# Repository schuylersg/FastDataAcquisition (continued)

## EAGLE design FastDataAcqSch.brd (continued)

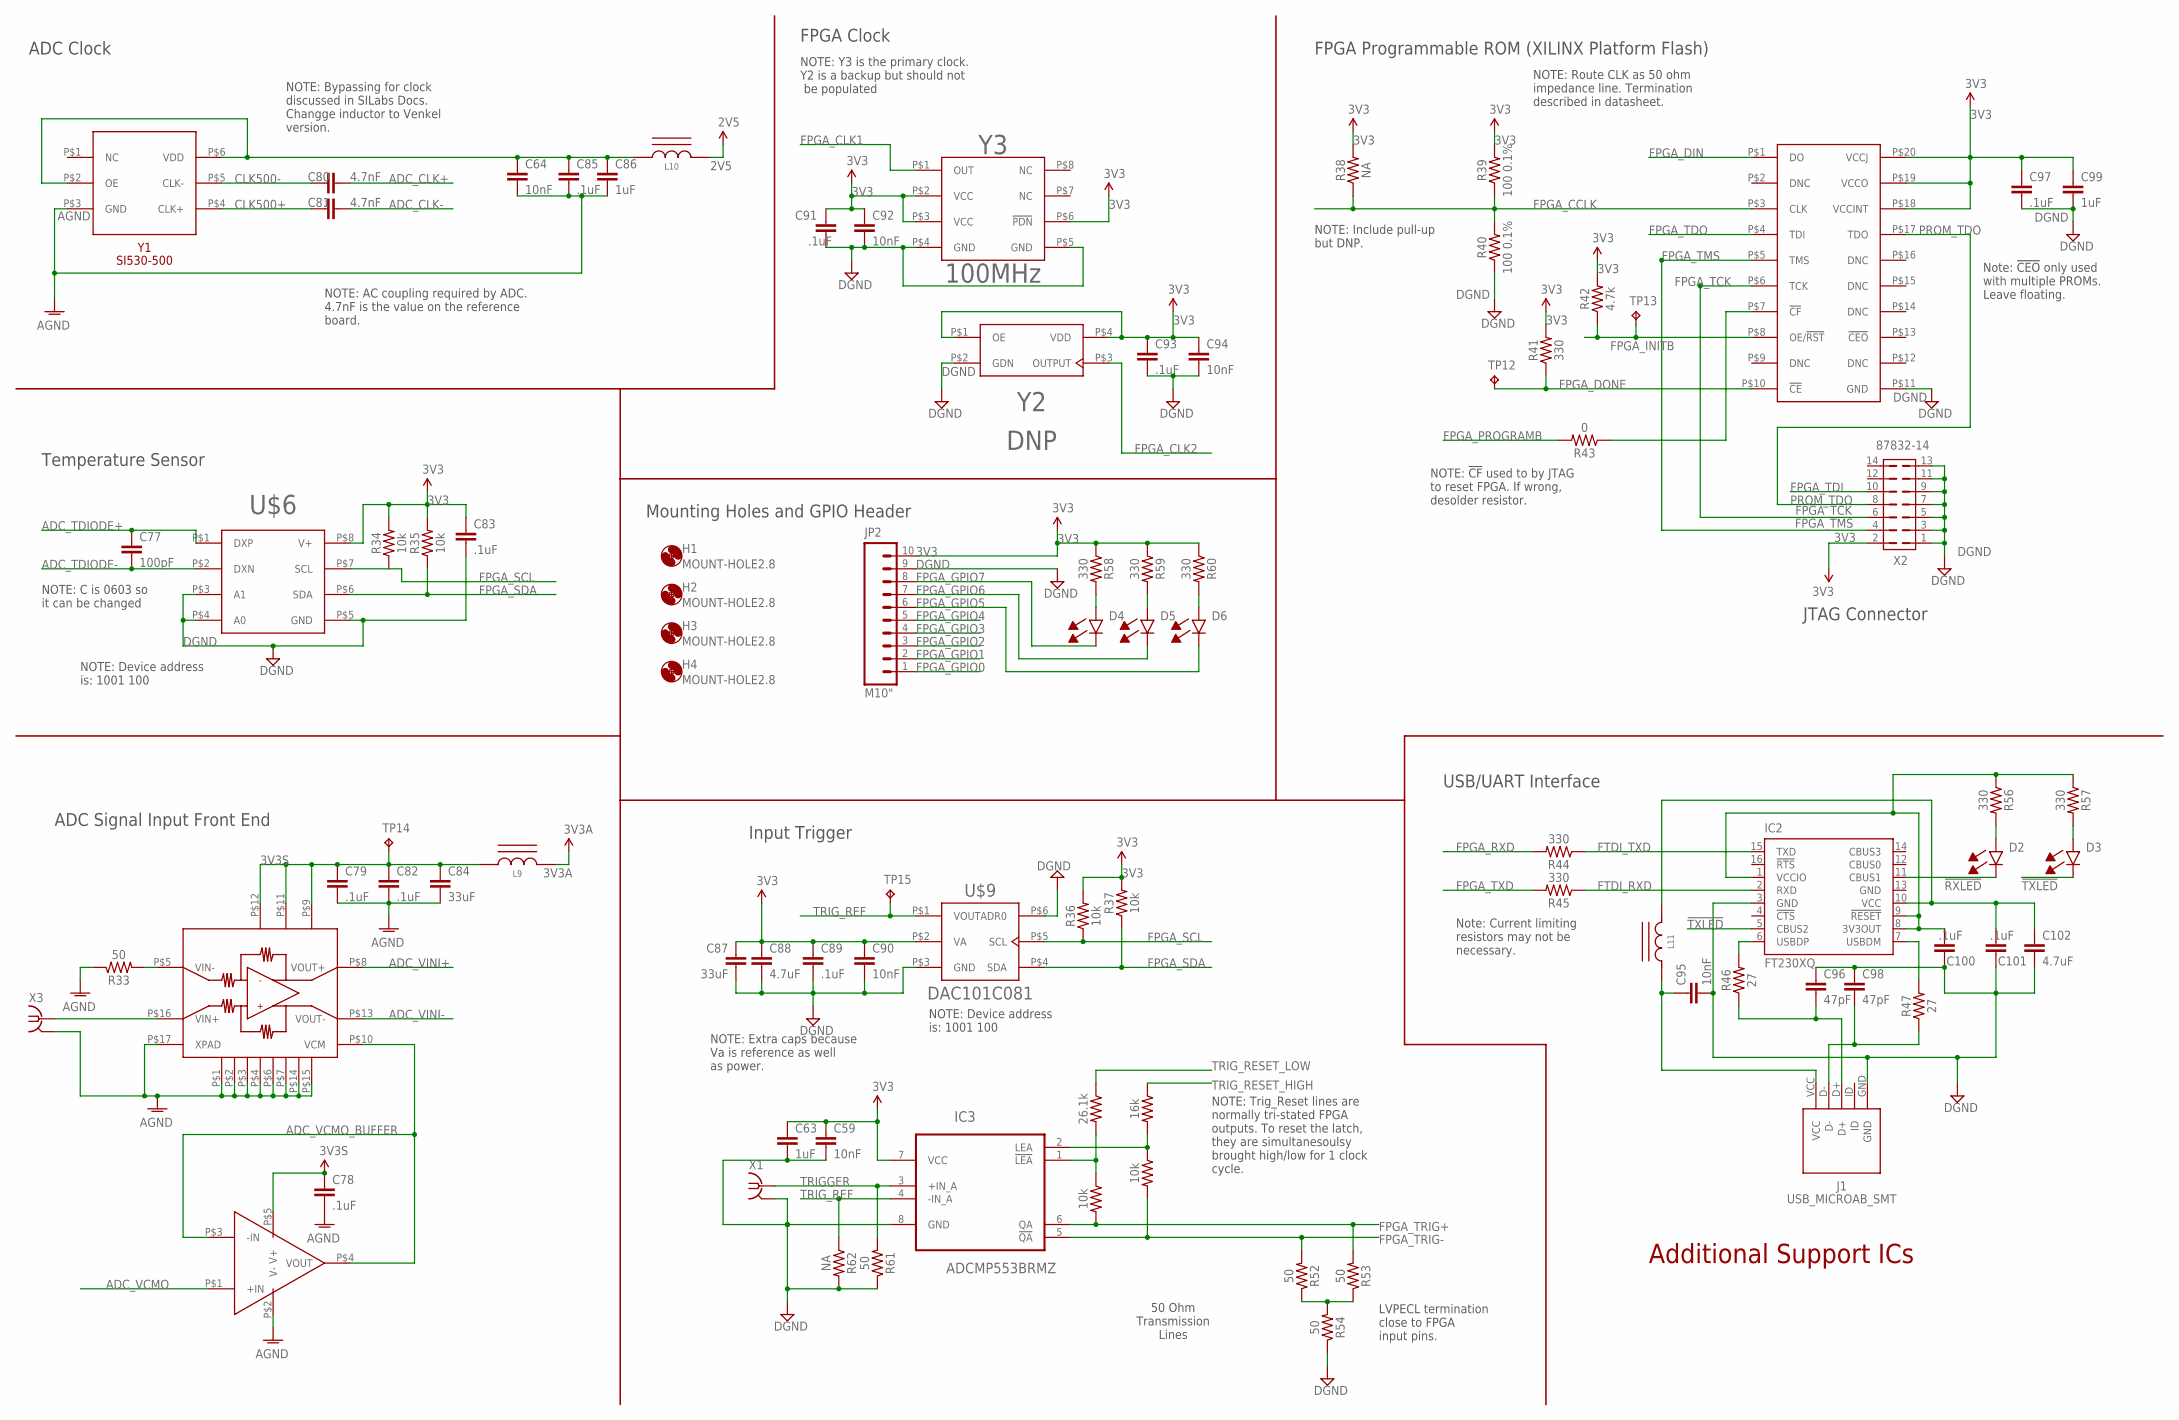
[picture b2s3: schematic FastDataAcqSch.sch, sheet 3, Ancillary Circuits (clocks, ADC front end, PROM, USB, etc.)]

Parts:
C59, C64, C90, C92, C94, C95: 10nF; C0201; PARTNUMBER 445-1793-1-ND
C63, C86, C99: 1uF; 0204REVERSE; PARTNUMBER 445-9091-1-ND
C77: 100pF; C0603; PARTNUMBER 1276-1295-1-ND
C78, C79, C82, C83, C85, C89, C91, C93, C97, C100, C101: .1uF; 0204REVERSE; PARTNUMBER 587-2152-1-ND
C80, C81: 4.7nF; C0201; PARTNUMBER 445-1795-1-ND
C84, C87: 33uF; 0805; PARTNUMBER 445-8238-1-ND
C88, C102: 4.7uF; 0306REVERSE; PARTNUMBER 445-13745-1-ND
C96, C98: 47pF; C0201; PARTNUMBER 445-1782-1-ND
D2, D5: LED_0603_GREEN; 0603_LED
D3, D4: LED_0603_BLUE; 0603_LED
D6: LED_0603_RED; 0603_LED
H1, H2, H3, H4: MOUNT-HOLE2.8; 2,8
IC2: FT230XQ; QFN16
IC3: ADCMP553BRMZ; SOP65P490X110-8N
J1: USB_MICROAB_SMT; USB_MICROAB_SMT_1
JP2: M10"; 1X10
L9, L10: FERRITE_BEADS_BLM18SG260; MURATA_BLM18
L11: FERRITE_BEADS_BLM18SG331; MURATA_BLM18
R33, R52, R53, R54, R61: 50; R0201; MANPARTNUMBER RC0603F49R9C
R34, R35, R36, R37: 10k; R0201; MANPARTNUMBER RC0603J103CS
R38: NA; R0603
R39, R40: 100 0.1%; R0402; MANPARTNUMBER ERA-2AEB101X
R41, R44, R45, R56, R57, R58, R59, R60: 330; R0201; MANPARTNUMBER RC0603J331CS
R42: 4.7k; R0201; MANPARTNUMBER ERJ-1GNJ472C
R43: 0; R0603; PARTNUMBER 311-0.0GRCT-ND
R46, R47: 27; R0201; PARTNUMBER 1276-3577-1-ND
R48, R50: 10k; R0603; PARTNUMBER 311-0.0GRCT-ND
R49: 26.1k; R0603; PARTNUMBER 311-0.0GRCT-ND
R51: 16k; R0603; PARTNUMBER 311-0.0GRCT-ND
R62: NA; R0603; PARTNUMBER 311-0.0GRCT-ND
TP12, TP13, TP14, TP15: TPPAD1-13; P1-13
U$6: TMP421; SOT23-8
U$7: LMH6555; 16WQFN
U$8: LMV321SC-70; SC-70
U$9: DAC101C081; SOT23-6
U$10: XCFXXS04; TSSOP20_XILINX
X1, X3: SMA-142-0701-801/806; J502-ND-142-0701-801/806; MANPARTNUMBER 142-0701-801
X2: 87832-14; PARTNUMBER 57J0374
Y1: SI530-500; SI530
Y2: DNP; SI500S
Y3: 100MHz; UMAX8

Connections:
2V5: L10.P$2; also elsewhere on the board
2V5A: C64.1, C85.P$1 (1), C86.P$1 (1), L10.P$1, Y1.P$2 (OE), Y1.P$6 (VDD)
3V3: C59.1, C63.P$1 (1), C83.P$1 (1), C87.1, C88.P$1 (1), C89.P$1 (1), C90.1, C91.P$1 (1), C92.1, C93.P$1 (1), C94.1, C97.P$1 (1), C99.P$1 (1), IC3.7 (VCC), JP2.10, R35.2, R36.2, R37.2, R38.2, R39.2, R41.2, R58.1, R59.1, R60.1, U$6.P$8 (V+), U$9.P$2 (VA), U$10.P$18 (VCCINT), U$10.P$19 (VCCO), U$10.P$20 (VCCJ), X2.2, Y2.P$1 (OE), Y2.P$4 (VDD), Y3.P$2 (VCC), Y3.P$3 (VCC), Y3.P$6 (!PDN); also elsewhere on the board
3V3A: L9.P$2; also elsewhere on the board
3V3S: C78.P$1 (1), C79.P$1 (1), C82.P$1 (1), C84.1, L9.P$1, TP14.TP, U$7.P$9 (VCC), U$7.P$11 (VCC), U$7.P$12 (VCC), U$8.P$5 (V+)
5VUSB: C101.P$2 (2), C102.P$1 (1), IC2.10 (VCC), L11.P$2
5VUSB_CON: C95.1, J1.VCC, L11.P$1
!RXLED: D2.CATHODE, IC2.11 (CBUS1)
!TXLED: D3.CATHODE, IC2.5 (CBUS2)
ADC_CLK+: C80.2; also elsewhere on the board
ADC_CLK-: C81.2; also elsewhere on the board
ADC_TDIODE+: C77.1, U$6.P$1 (DXP); also elsewhere on the board
ADC_TDIODE-: C77.2, U$6.P$2 (DXN); also elsewhere on the board
ADC_VCMO: U$8.P$1 (+IN); also elsewhere on the board
ADC_VCMO_BUFFER: U$7.P$10 (VCM), U$8.P$3 (-IN), U$8.P$4 (VOUT); also elsewhere on the board
ADC_VINI+: U$7.P$8 (VOUT+); also elsewhere on the board
ADC_VINI-: U$7.P$13 (VOUT-); also elsewhere on the board
AGND: C64.2, C78.P$2 (2), C79.P$2 (2), C82.P$2 (2), C84.2, C85.P$2 (2), C86.P$2 (2), R33.1, U$7.P$1 (GND), U$7.P$2 (GND), U$7.P$3 (GND), U$7.P$4 (GND), U$7.P$6 (GND), U$7.P$7 (GND), U$7.P$14 (GND), U$7.P$15 (GND), U$7.P$17 (XPAD), U$8.P$2 (V-), X3.G@1 (2), X3.G@2 (2), X3.G@3 (2), X3.G@4 (2), Y1.P$3 (GND); also elsewhere on the board
CLK500+: C81.1, Y1.P$4 (CLK+)
CLK500-: C80.1, Y1.P$5 (CLK-)
DGND: C59.2, C63.P$2 (2), C83.P$2 (2), C87.2, C88.P$2 (2), C89.P$2 (2), C90.2, C91.P$2 (2), C92.2, C93.P$2 (2), C94.2, C95.2, C96.1, C97.P$2 (2), C98.1, C99.P$2 (2), C100.P$1 (1), C101.P$1 (1), C102.P$2 (2), IC2.3 (GND), IC3.8 (GND), J1.GND, JP2.9, R40.1, R54.1, R61.1, R62.2, U$6.P$3 (A1), U$6.P$4 (A0), U$6.P$5 (GND), U$9.P$3 (GND), U$9.P$6 (ADR0), U$10.P$11 (GND), X1.G@1 (2), X1.G@2 (2), X1.G@3 (2), X1.G@4 (2), X2.1, X2.3, X2.5, X2.7, X2.9, X2.11, X2.13, Y2.P$2 (GDN), Y3.P$4 (GND), Y3.P$5 (GND); also elsewhere on the board
FPGA_CCLK: R38.1, R39.1, R40.2, U$10.P$3 (CLK); also elsewhere on the board
FPGA_CLK1: Y3.P$1 (OUT); also elsewhere on the board
FPGA_CLK2: Y2.P$3 (OUTPUT); also elsewhere on the board
FPGA_DIN: U$10.P$1 (DO); also elsewhere on the board
FPGA_DONE: R41.1, TP12.TP, U$10.P$10 (!CE); also elsewhere on the board
FPGA_GPIO0: JP2.1; also elsewhere on the board
FPGA_GPIO1: JP2.2; also elsewhere on the board
FPGA_GPIO2: JP2.3; also elsewhere on the board
FPGA_GPIO3: JP2.4; also elsewhere on the board
FPGA_GPIO4: JP2.5; also elsewhere on the board
FPGA_GPIO5: D6.CATHODE, JP2.6; also elsewhere on the board
FPGA_GPIO6: D5.CATHODE, JP2.7; also elsewhere on the board
FPGA_GPIO7: D4.CATHODE, JP2.8; also elsewhere on the board
FPGA_INITB: TP13.TP, U$10.P$8 (OE/!RST); also elsewhere on the board
FPGA_PROGRAMB: R43.2; also elsewhere on the board
FPGA_RXD: R44.2; also elsewhere on the board
FPGA_SCL: R36.1, U$6.P$7 (SCL), U$9.P$5 (SCL); also elsewhere on the board
FPGA_SDA: R35.1, R37.1, U$6.P$6 (SDA), U$9.P$4 (SDA)
FPGA_TCK: U$10.P$6 (TCK), X2.6; also elsewhere on the board
FPGA_TDI: X2.10; also elsewhere on the board
FPGA_TDO: U$10.P$4 (TDI); also elsewhere on the board
FPGA_TMS: U$10.P$5 (TMS), X2.4; also elsewhere on the board
FPGA_TRIG+: IC3.6 (QA), R48.2, R53.2; also elsewhere on the board
FPGA_TRIG-: IC3.5 (!QA), R50.2, R52.2; also elsewhere on the board
FPGA_TXD: R45.2; also elsewhere on the board
FTDI_RXD: IC2.2 (RXD), R45.1
FTDI_TXD: IC2.15 (TXD), R44.1
GND: IC2.13 (GND)
unnamed: R33.2, U$7.P$5 (VIN-)
unnamed: IC2.6 (USBDP), R46.2
unnamed: C96.2, J1.D+, R46.1
unnamed: C98.2, J1.D-, R47.1
unnamed: IC2.7 (USBDM), R47.2
unnamed: C100.P$2 (2), IC2.1 (VCCIO), IC2.8 (3V3OUT), IC2.9 (!RESET), R56.1, R57.1
unnamed: D2.ANODE, R56.2
unnamed: R43.1, U$10.P$7 (!CF)
unnamed: D3.ANODE, R57.2
unnamed: IC3.1 (!LEA), R48.1, R49.2
unnamed: R52.1, R53.1, R54.2
unnamed: D6.ANODE, R60.2
unnamed: IC3.2 (LEA), R50.1, R51.2
unnamed: D5.ANODE, R59.2
unnamed: D4.ANODE, R58.2
PROM_TDO: U$10.P$17 (TDO), X2.8
SIGNAL_IN: U$7.P$16 (VIN+), X3.1
TRIGGER: IC3.3 (+IN_A), R61.2, X1.1
TRIG_REF: IC3.4 (-IN_A), R62.1, TP15.TP, U$9.P$1 (VOUT)
TRIG_RESET_HIGH: R51.1
TRIG_RESET_LOW: R49.1

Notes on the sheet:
NOTE: Bypassing for clock discussed in SILabs Docs. Changge inductor to Venkel version.
ADC Clock
NOTE: AC coupling required by ADC. 4.7nF is the value on the reference board.
ADC Signal Input Front End
NOTE: Route CLK as 50 ohm impedance line. Termination described in datasheet.
Note: !CEO! only used with multiple PROMs. Leave floating.
NOTE: !CF! used to by JTAG to reset FPGA. If wrong, desolder resistor.
FPGA Programmable ROM (XILINX Platform Flash)
JTAG Connector
NOTE: Include pull-up but DNP.
Note: Current limiting resistors may not be necessary.
USB/UART Interface
FPGA Clock
NOTE: Y3 is the primary clock. Y2 is a backup but should not be populated
NOTE: C is 0603 so it can be changed
Temperature Sensor
Input Trigger
NOTE: Device address is: 1001 100
NOTE: Extra caps because Va is reference as well as power.
50 Ohm Transmission Lines
LVPECL termination close to FPGA input pins.
NOTE: Trig_Reset lines are normally tri-stated FPGA outputs. To reset the latch, they are simultanesoulsy brought high/low for 1 clock cycle.
Additional Support ICs
Mounting Holes and GPIO Header

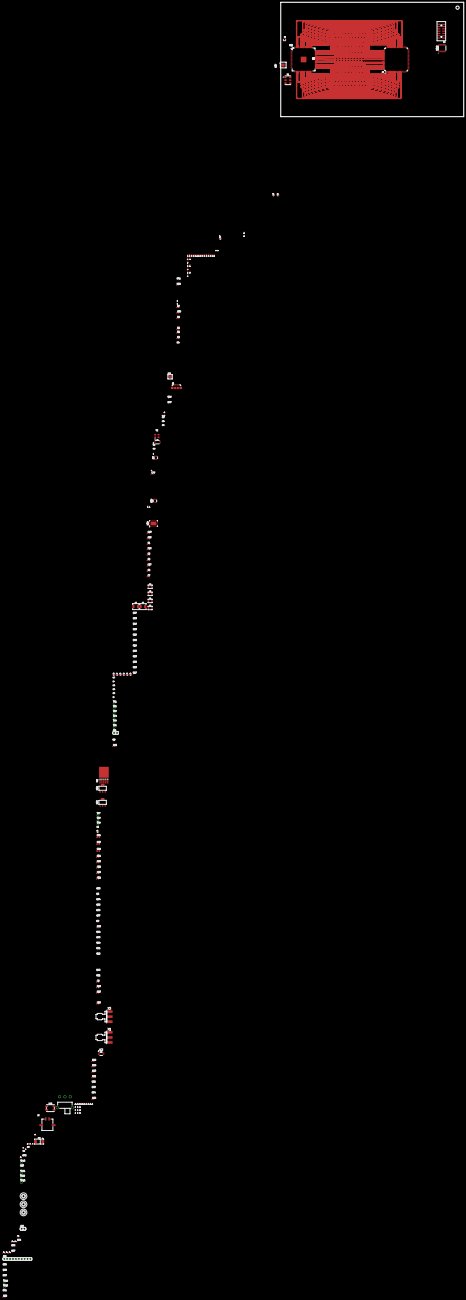
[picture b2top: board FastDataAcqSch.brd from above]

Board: 4 copper layers, 229 parts (1 on the bottom side), 181 nets.

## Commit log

2013-08-31 Initial Commit
    The first commit of the fast data acquisition (FDA) board. Schematic is
    ~80% complete and board layout is 10%. Repository is largely for backup
    purpose at this point.
2013-09-01 Update from end of day 8/31
    Added USB/UART interface.
2013-09-03 Update 9/2/13
    Added more ICs
2013-09-18 Nearly finalized schematic
2013-09-18 Only 9 parts left to source
2013-09-19 Schematic Finalized
2013-09-24 Changed Ferrites plus some peripherals
2013-09-24 Unchecked Finalized Schematic
2013-09-26 Renamed files, include PDF
2013-09-27 Schematic fixes and beginning board layout
2013-09-28 Board layout in progress. Other minor fixes.
2013-10-02 Minor schematic fixes, major PCB layout changes
2013-10-03 Now includes python layout scripts
2013-10-03 New bypass layout
2013-10-03 New power switch layout
2013-10-04 Component placement semi-finalized
2013-10-05 Board layout almost complete.
    Power plane almost routes all the power correctly.
2013-10-08 Continued board layout
2013-10-08 Digital routing almost done.
2013-10-09 Digital layout complete.
2013-10-11 PCB v0.1 done
    Still need to fix a few things, but technically routing is done.
2013-11-10 Several changes
    There are several changes after discussing the design with Grant
    Elliott. Most notably is the addition of a On/Off Debounce Latch IC.
    Additionally the CTS is now connected to the FPGA to force the packet to
    be sent.
2013-11-12 PCB Power Layer and Other Fixes
    Finalized the FPGA GPIO Pins. Fixed power layer so that all spacing is
    equal and entire layer covered. Other cosmetic fixes.
2013-11-12 LVDS Top Changed
    Changed LVDS data lines to 5mil width and spacing. Bend separation is
    25mil. Only the top data lines are finished - still need to do the
    bottom and sides.
2013-11-13 Partially done with LVDS bottom half.
2013-11-14 Finished LVDS layout.
    Making additional final changes. Still need to add test points.
2013-11-15 Parts finalized. Layout near done.
    Still a few things on the to do list, but most tracks are final. Still
    need test points and to go over all text that's getting printed.
2013-11-15 FDA v0.9 Ready For Quote Submission
    All that is left is shielding mounting holes.
2013-11-16 Neatened back traces.
2013-11-18 Minor Changes - Fixed Screw Holes
2013-11-18 More minor fixes.
2013-11-19 Ready for quote submittal.
2013-11-19 Fixed consistency issue between sch and brd
2013-11-22 Done with adjusting most of the LVDS track widths.
2013-11-22 Bottom LVDS traces optimized
2013-11-22 Few minor changes
2013-11-22 Minor changes.
2013-11-22 Minor Changes'
2013-11-22 Minor
2013-11-22 Fixed unrouted signal.
2013-11-22 v1.0s complete
    Ready to submit for fab.
2013-12-23 Minor fixes
    Changed some signals names.
2014-07-14 Final Commit from v1.0
    Final commit for version 1.0 after testing completed.
2014-07-14 Minor fixes and changes for v1.1
    See v1.1. changes.txt for full details.
2014-07-15 Updates to BOM
    Resistor part numbers changed.
